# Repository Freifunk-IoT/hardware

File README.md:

# Freifunk-IoT-Hardware

| Hardware/Details                 | Typ  | Messungen/Sensor                                             | Stückpreis ca. | Status                | Bemerkungen                                                  |
| -------------------------------- | ---- | ------------------------------------------------------------ | -------------- | --------------------- | ------------------------------------------------------------ |
| [ESP-03 mit BME280](https://github.com/Freifunk-IoT/hardware/blob/master/esp8266/enviroment/esp03_bme280/ESP03_BME280.md)            | PCB  | BME280 (Temperatur, Luftfeuchtigkeit, Luftdruck)             | ?              | funktioniert (Rev. 2) | kann Deep Sleep, inkl. Sicherung                             |
| ESP-03 mit BME280/DHT22 (Hybrid) | PCB  | BME280 (Temperatur, Luftfeuchtigkeit, Luftdruck) oder DHT22 (Temperatur, Luftfeuchtigkeit) | ?              | Idee                  |                                                              |
| ESP-01 mit DHT11                 | Mod  | DHT22 (T)                                                    | ?              | Idee                  | Modul gibt es fertig bei Aliexpress etc., vmtl. gut für den "schnellen Einstieg". |
| [ESP-01 mit DHT*/BME280 "Workshop Board"](https://github.com/Freifunk-IoT/hardware/blob/master/esp8266/enviroment/esp01_DHT22_USB/ESP01_DHT22.md) | PCB  | BME280 (Temperatur, Luftfeuchtigkeit, Luftdruck) oder DHT22 (Temperatur, Luftfeuchtigkeit) | ?              | Hardware funktioniert und ist getestet, Software fehlt                  | Einsteigerplatine mit Linearregler (USB-Anschluss) + entsprechende Absicherung, wahlweise BME280 oder DHT*, kleinste Bauteile: 1206, alles andere THT |
| Outdoor-Full-Feature-Board       | PCB  | BME280                                                       | ?              | Idee                  | inkl. BMS für LiIon, Spannungsreglern (Buck/Boost), Absicherungen, Deep Sleep, optimiert für lange Laufzeiten |
| Wemos D1 mini mit DHT* | PCB | DHT* (Temperatur + Feuchtigkeit) | ? | Idee | Für einfachen Einstieg (5V USB Eingang) |

Wenn du Freifunk-IoT auf anderer Hardware betreibst, neue Sensoren eingebunden hast, eine praktische Platine entworfen hast oder einfach nur dein Aufbau vorstellen willst, mach einfach einen eigenen Ordner für dein Projekt auf und stelle es vor!

*Bitte beachtet: Dieses Repository ist mehr für die technische Entwicklung und Vorstellung gedacht. Reine Tutorials sind auf der [website](https://github.com/Freifunk-IoT/website) besser aufgehoben.*

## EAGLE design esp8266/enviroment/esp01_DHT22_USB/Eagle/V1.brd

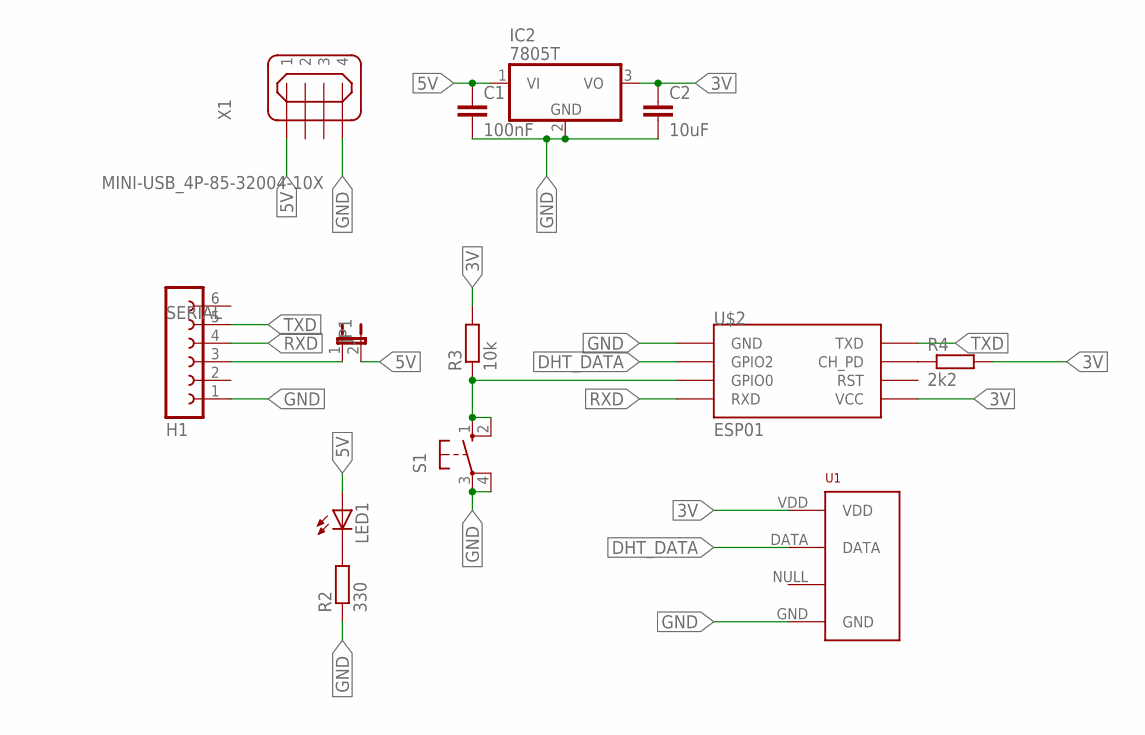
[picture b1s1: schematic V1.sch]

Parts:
C1: 100nF; C025-030X050
C2: 10uF; C025-030X050
IC2: 7805T; TO220H
JP1: JP1E; JP1
LED1: LED5MM
R2: 330; 0207/10
R3: 10k; 0207/10
R4: 2k2; 0207/10
S1: 10-XX; B3F-10XX
SERIAL: H1; FE06
U1: RHT03_DHT-22_AM2302; RHT03_DHT-22
U$2: ESP01
X1: MINI-USB_4P-85-32004-10X; 85-32004-10X

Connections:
3V: C2.1, IC2.3 (VO), R3.2, R4.2, U1.VDD, U$2.VCC
5V: C1.1, IC2.1 (VI), JP1.2, LED1.A, X1.1
DHT_DATA: U1.DATA, U$2.GPIO2
GND: C1.2, C2.2, IC2.2 (GND), R2.1, S1.3, S1.4 (P1), SERIAL.1, U1.GND, U$2.GND, X1.4
unnamed: JP1.1, SERIAL.3
unnamed: LED1.K (C), R2.2
unnamed: R3.1, S1.1 (S), S1.2 (S1), U$2.GPIO0
unnamed: R4.1, U$2.CH_PD
RXD: SERIAL.4, U$2.RX (RXD)
TXD: SERIAL.5, U$2.TX (TXD)

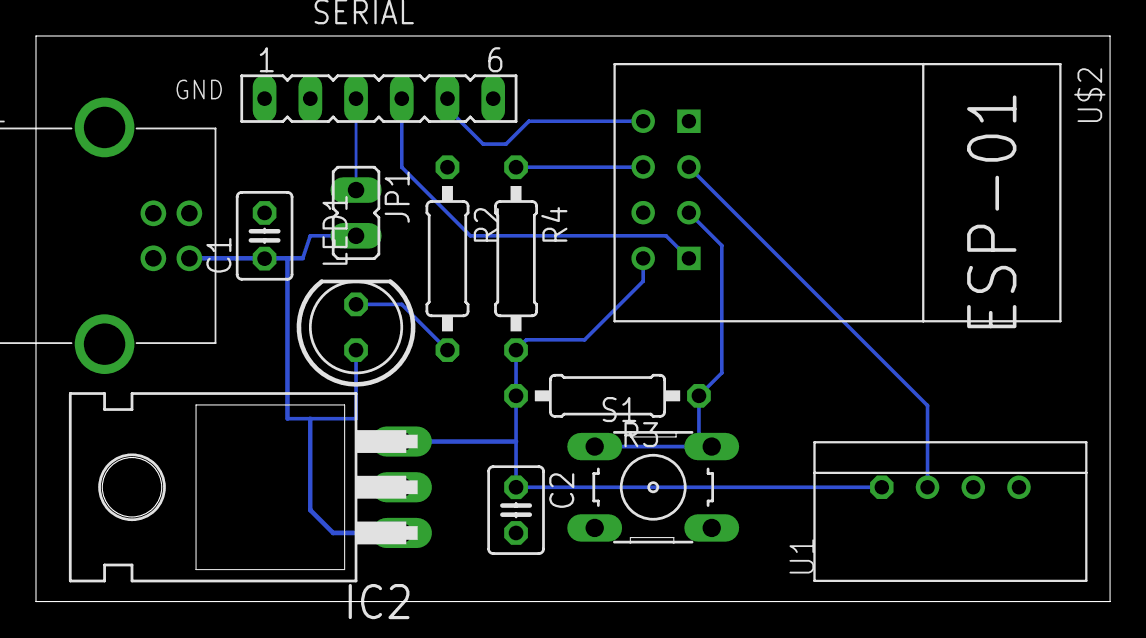
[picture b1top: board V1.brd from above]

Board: 2 copper layers, 59.7 x 31.4 mm, 13 parts (0 on the bottom side), 10 nets.

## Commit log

2018-07-27 Added some text to readme
2018-07-27 Started to describe ESP03-BME280
2018-07-27 Fix image URLs
2018-07-27 Fix Link URL
2018-07-28 Added Gerber
2018-07-28 Added Image
2018-07-28 Fixed mention
2018-07-28 added "Wemos D1 mini mit DHT*"
2018-07-28 Added Workshop-Board
2018-10-29 First commit for Workshop-Board
2018-10-29 Update ESP01_DHT22.md
    Fixed Markdown
2018-10-29 Update README.md
    Updated Readme.md
2018-10-29 Changed Programmer-Pinout
2018-10-29 Update ESP01_DHT22.md
    Updated Partslist
2018-12-01 Changed Voltage-Regulator to fit pseudo-standart pinout
2018-12-01 Update ESP01_DHT22.md
    Fixed Description
2018-12-08 Update README.md
    Updated infos about the "Workshop-board"
2018-12-22 Added Software
